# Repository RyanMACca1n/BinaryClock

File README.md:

# BinaryClock
small micro controller project for a binary / BCD clock

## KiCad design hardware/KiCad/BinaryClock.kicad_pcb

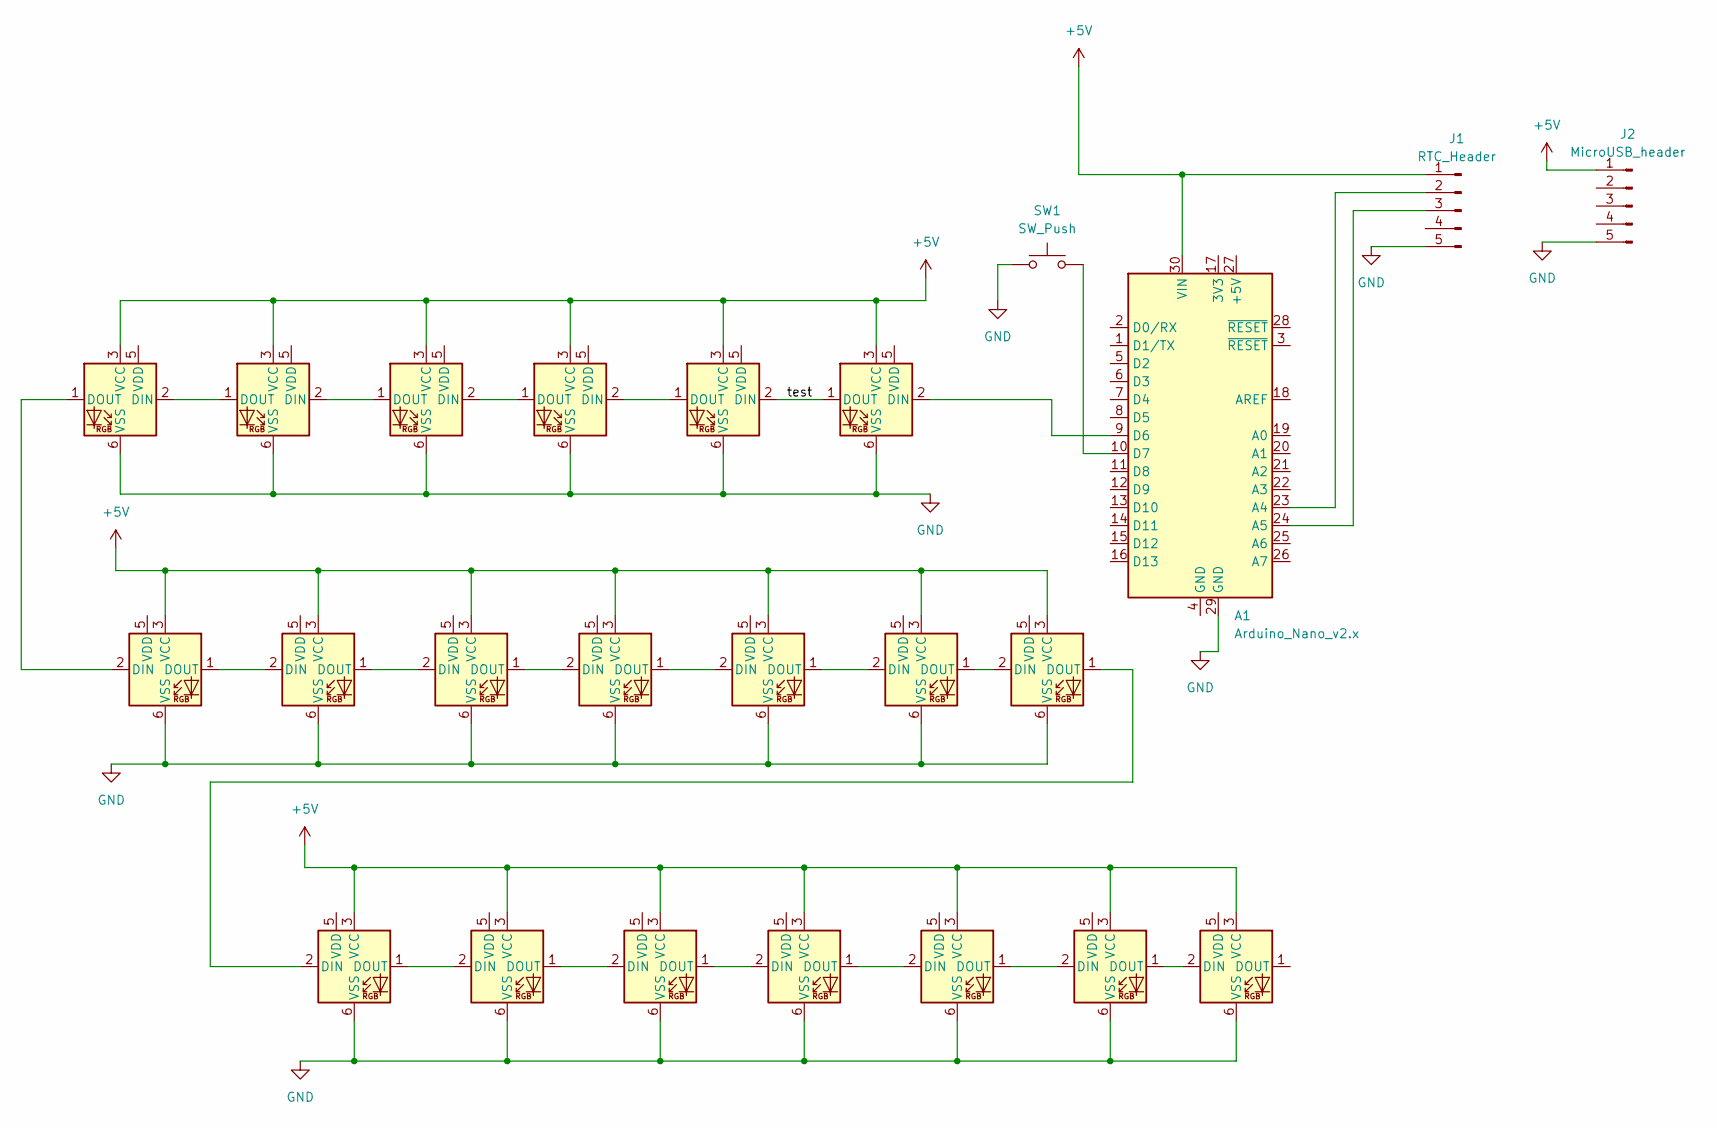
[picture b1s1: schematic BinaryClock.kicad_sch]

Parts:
A1: Arduino_Nano_v2.x; Arduino_Nano
D1, D2: WS2812; LED_D5.0mm-4_RGB_WS2811
D3, D4, D5, D6, D7, D8, D9, D10, D11, D12, D13, D14, D15, D16, D17, D18, D19, D20: WS2812; LED_WS2812_PLCC6_5.0x5.0mm_P1.6mm
J1: RTC_Header; PinHeader_1x05_P2.54mm_Vertical
J2: MicroUSB_header; PinHeader_1x05_P2.54mm_Vertical
SW1: SW_Push; SW_PUSH_6mm

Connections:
+5V: A1.30 (VIN), D1.3 (VCC), D2.3 (VCC), D3.3 (VCC), D4.3 (VCC), D5.3 (VCC), D6.3 (VCC), D7.3 (VCC), D8.3 (VCC), D9.3 (VCC), D10.3 (VCC), D11.3 (VCC), D12.3 (VCC), D13.3 (VCC), D14.3 (VCC), D15.3 (VCC), D16.3 (VCC), D17.3 (VCC), D18.3 (VCC), D19.3 (VCC), D20.3 (VCC), J1.1, J2.1
GND: A1.29 (GND), D1.6 (VSS), D2.6 (VSS), D3.6 (VSS), D4.6 (VSS), D5.6 (VSS), D6.6 (VSS), D7.6 (VSS), D8.6 (VSS), D9.6 (VSS), D10.6 (VSS), D11.6 (VSS), D12.6 (VSS), D13.6 (VSS), D14.6 (VSS), D15.6 (VSS), D16.6 (VSS), D17.6 (VSS), D18.6 (VSS), D19.6 (VSS), D20.6 (VSS), J1.5, J2.5, SW1.1
unnamed: A1.23 (A4), J1.2
unnamed: A1.24 (A5), J1.3
unnamed: A1.9 (D6), D1.2 (DIN)
unnamed: A1.10 (D7), SW1.2
unnamed: D1.1 (DOUT), D2.2 (DIN)
unnamed: D2.1 (DOUT), D3.2 (DIN)
unnamed: D3.1 (DOUT), D4.2 (DIN)
unnamed: D4.1 (DOUT), D5.2 (DIN)
unnamed: D5.1 (DOUT), D6.2 (DIN)
unnamed: D6.1 (DOUT), D7.2 (DIN)
unnamed: D7.1 (DOUT), D8.2 (DIN)
unnamed: D8.1 (DOUT), D9.2 (DIN)
unnamed: D9.1 (DOUT), D10.2 (DIN)
unnamed: D10.1 (DOUT), D11.2 (DIN)
unnamed: D11.1 (DOUT), D12.2 (DIN)
unnamed: D12.1 (DOUT), D13.2 (DIN)
unnamed: D13.1 (DOUT), D14.2 (DIN)
unnamed: D14.1 (DOUT), D15.2 (DIN)
unnamed: D15.1 (DOUT), D16.2 (DIN)
unnamed: D16.1 (DOUT), D17.2 (DIN)
unnamed: D17.1 (DOUT), D18.2 (DIN)
unnamed: D18.1 (DOUT), D19.2 (DIN)
unnamed: D19.1 (DOUT), D20.2 (DIN)

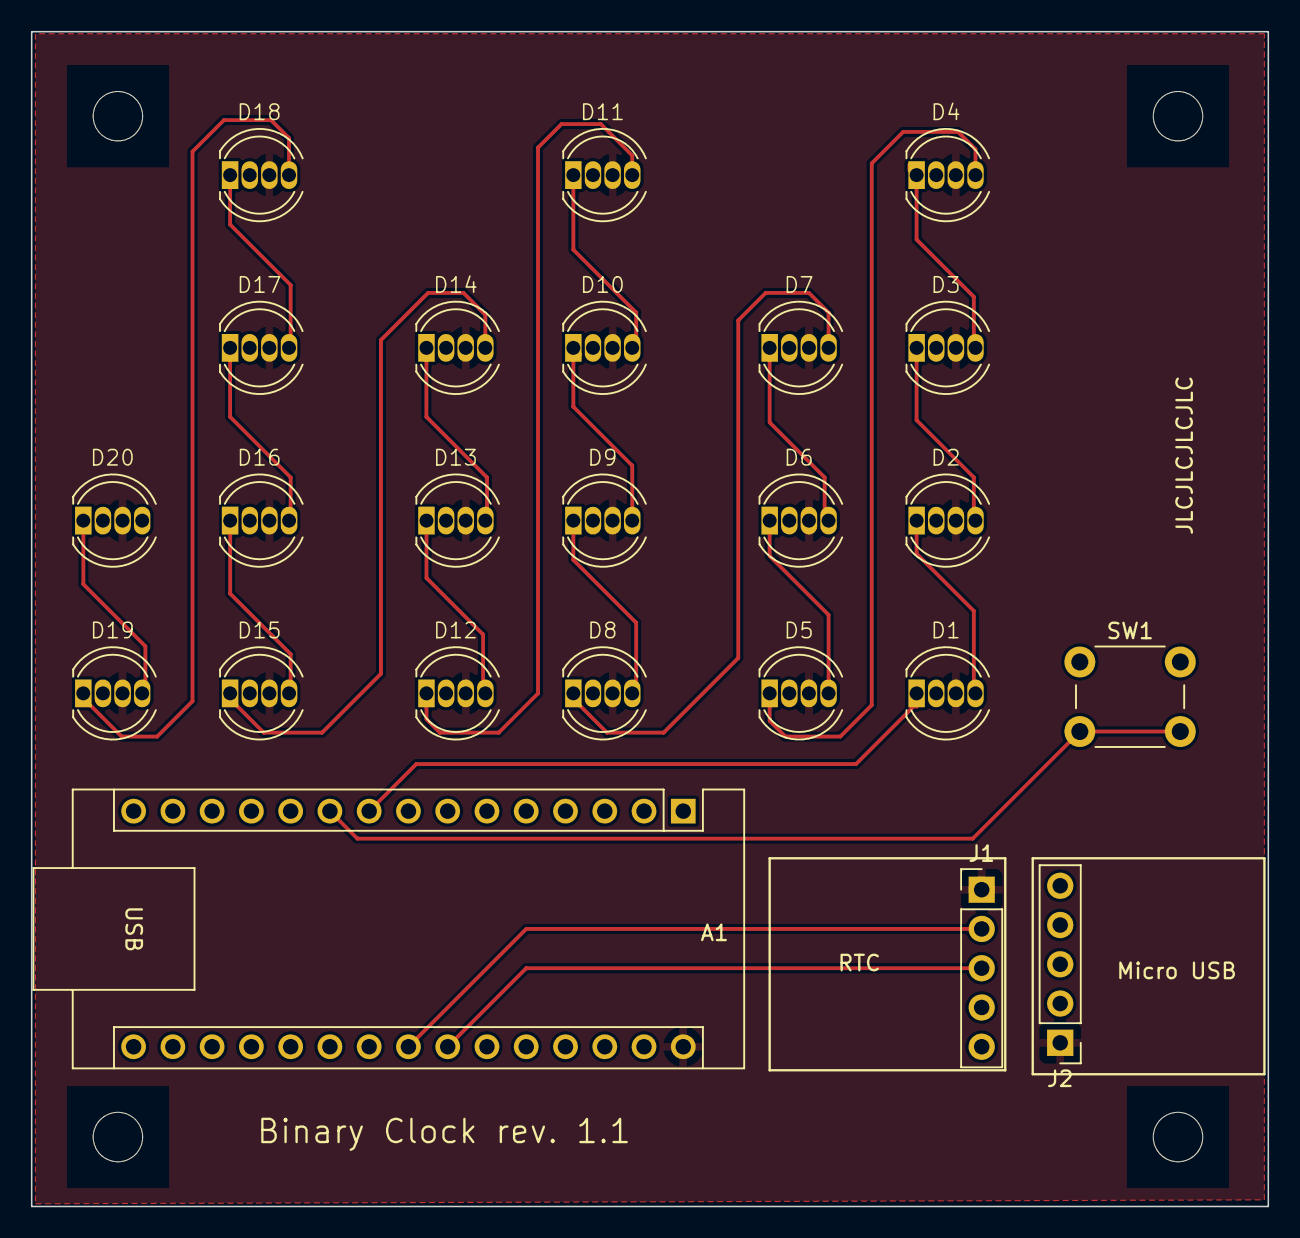
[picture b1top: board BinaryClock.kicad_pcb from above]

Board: 2 copper layers, 80.0 x 76.0 mm, 24 parts (0 on the bottom side), 25 nets.

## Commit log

2024-03-03 Add all arduino source files
    SetTime.ino is an example sketch used to set the time of the DS3231 RTC module beeing used
    clock.ino is the main sketch that runs the finished clock
    ledTest.ino is a simple sketch which tests all colors of two WS2811 LEDs and can be used to test the LEDs individually before soldering
2024-03-03 Initially add all files regarding the hardware
    Add all kicad files and ready archive containing all gerber files for
    the rev. 1.0 of the PCB
    Add the STL for a basic display stand
2024-03-04 fix: move .ino files into their respective folders for the Arduino IDE
2024-03-05 Delete src/SetTime.ino
    Remove duplicate file
2024-03-05 Delete src/ledTest.ino
    Remove duplicate file
2024-03-05 Delete src/clock.ino
    Remove duplicate file
2024-03-07 Update issue templates
2024-03-07 feat: add dynamic LED colouring when showing RTC temperature
    LED colouring has been implemented via four linear functions.
    This will mix the colours dependend on the temperature.
    The range for the temperature in the functions has been set
    from 0 to 40°C.
    The functions used are (x represents the temperature):
    Red = 12,75x - 255
